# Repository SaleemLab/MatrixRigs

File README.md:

# MatrixRigs
Docs related to setting up and running the matrix rigs

Contents:
- Hardware: wheel, lickport, screens + holders + nvidia mosiac, reward delivery. Parts list.
- Code: bonsai code e.g. screen set up, arduino code + serial read
- Maintenance: flushing reward etc.

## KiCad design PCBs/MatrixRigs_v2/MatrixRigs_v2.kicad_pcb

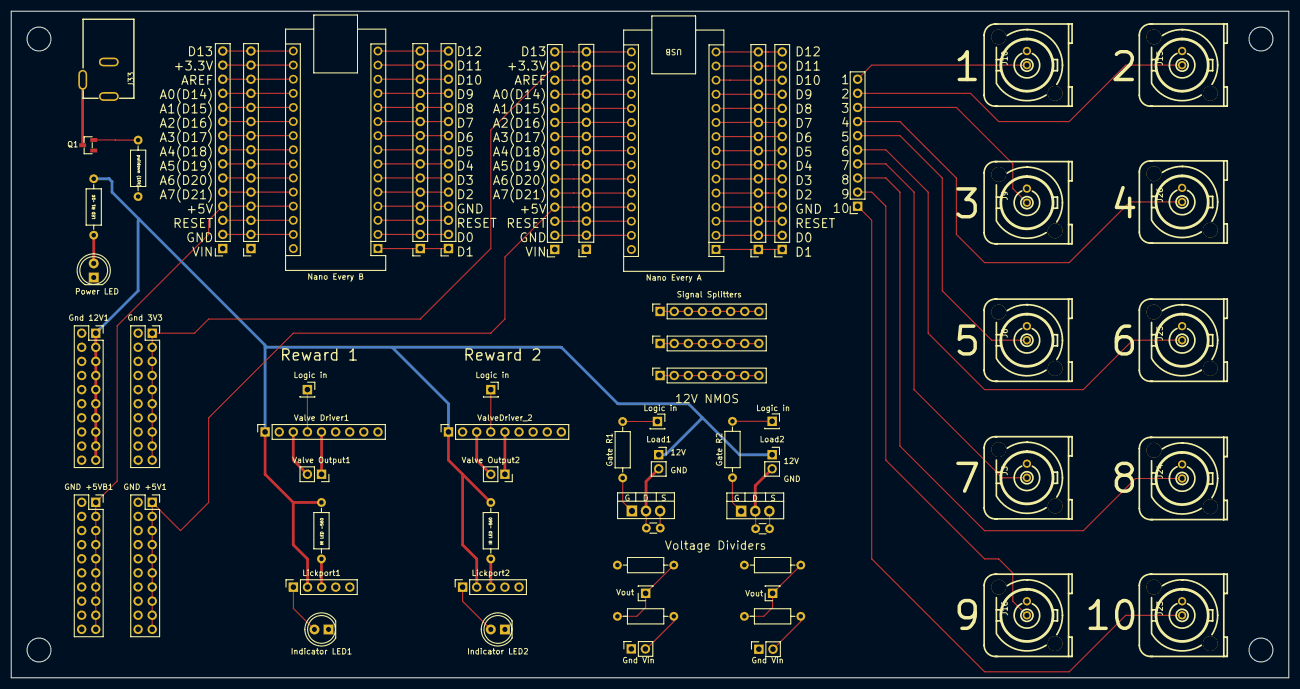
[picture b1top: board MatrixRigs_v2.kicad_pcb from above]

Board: 2 copper layers, 230.0 x 120.0 mm, 67 parts (0 on the bottom side), 92 nets.

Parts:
C1, C2: C; C_Disc_D3.0mm_W1.6mm_P2.50mm
D3: LED; LED_D5.0mm
GND +5V1, GND +5VB1: Conn_02x10_Top_Bottom; PinSocket_2x10_P2.54mm_Vertical
Gate R1, Gate R2: 10-100kohm; R_Axial_DIN0207_L6.3mm_D2.5mm_P10.16mm_Horizontal
Gnd 3V3, Gnd 12V1: Conn_02x10_Top_Bottom; PinSocket_2x10_P2.54mm_Vertical
H1, H2, H3, H4: MountingHole; MountingHole_4.3mm_M4
IR LED -1, IR LED -560: 560ohm; R_Axial_DIN0207_L6.3mm_D2.5mm_P10.16mm_Horizontal
Indicator LED1, Indicator LED2: LED; LED_D5.0mm
J1, J2, J27, J28, J29, J30, J31, J32: Conn_01x15_Socket; PinSocket_1x15_P2.54mm_Vertical
J3, J6, J9, J10, J15, J16, J23, J24, J25, J26: Conn_Coaxial; CONN-TH_1-1337541-0
J4: Conn_01x10_Socket; PinSocket_1x10_P2.54mm_Vertical
J7, J8: Conn_01x01_Socket; PinSocket_1x01_P2.54mm_Vertical
J12, J13: Conn_01x02_Socket; PinSocket_1x02_P2.54mm_Vertical
J33: Barrel_Jack_Switch_Pin3Ring; DC-IN-TH_XDJK-0051-025
LED R1 ~1K: 1kohm; R_Axial_DIN0207_L6.3mm_D2.5mm_P10.16mm_Horizontal
Lickport1, Lickport2: Conn_01x05_Socket; PinSocket_1x05_P2.54mm_Vertical
Load1, Load2: Conn_01x02_Socket; PinSocket_1x02_P2.54mm_Vertical
NMOS-T220: NMOS; TO-220-3_Vertical
Nano Every A: Arduino_Nano_v3.A; Arduino_Nano
Nano Every B: Arduino_Nano_v3.B; Arduino_Nano
Q1: PMOS; SOT-23-3_L2.9-W1.3-P1.90-LS2.4-BR
Q3: NMOS; TO-220-3_Vertical
R8: 10-100kohm; R_Axial_DIN0207_L6.3mm_D2.5mm_P10.16mm_Horizontal
Signal Splitters: Conn_01x08_Pin; PinSocket_1x08_P2.54mm_Vertical
SignalSplitter2, SignalSplitter3: Conn_01x08_Pin; PinSocket_1x08_P2.54mm_Vertical
Valve Driver1: Conn_01x09_Socket; PinSocket_1x09_P2.54mm_Vertical
Valve Output1, Valve Output2: Conn_01x02_Socket; PinSocket_1x02_P2.54mm_Vertical
Valve logic in1, Valve logic in2: Conn_01x01_Socket; PinSocket_1x01_P2.54mm_Vertical
ValveDriver_2: Conn_01x09_Socket; PinSocket_1x09_P2.54mm_Vertical
VoltageDivider_R1_1, VoltageDivider_R1_2: R; R_Axial_DIN0207_L6.3mm_D2.5mm_P10.16mm_Horizontal
VoltageDivider_R2_1: VoltageDivider_R2_1; R_Axial_DIN0207_L6.3mm_D2.5mm_P10.16mm_Horizontal
VoltageDivider_R2_2: VoltageDivider_R2_2; R_Axial_DIN0207_L6.3mm_D2.5mm_P10.16mm_Horizontal
Vout: Conn_01x01_Socket; PinSocket_1x01_P2.54mm_Vertical
Vout#2: Conn_01x01_Socket; PinSocket_1x01_P2.54mm_Vertical

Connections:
+3V3: Gnd 3V3.1, Gnd 3V3.3, Gnd 3V3.5, Gnd 3V3.7, Gnd 3V3.9, Gnd 3V3.11, Gnd 3V3.13, Gnd 3V3.15, Gnd 3V3.17, Gnd 3V3.19, J2.14, J32.14, Nano Every A.17 (3V3)
+3V3_B: J28.14, J30.14, Nano Every B.17 (3V3)
+5V: GND +5V1.1, GND +5V1.3, GND +5V1.5, GND +5V1.7, GND +5V1.9, GND +5V1.11, GND +5V1.13, GND +5V1.15, GND +5V1.17, GND +5V1.19, J2.4, J32.4, Nano Every A.27 (+5V)
+5V_B: GND +5VB1.1, GND +5VB1.3, GND +5VB1.5, GND +5VB1.7, GND +5VB1.9, GND +5VB1.11, GND +5VB1.13, GND +5VB1.15, GND +5VB1.17, GND +5VB1.19, J28.4, J30.4, Nano Every B.27 (+5V)
+12V: Gnd 12V1.1, Gnd 12V1.3, Gnd 12V1.5, Gnd 12V1.7, Gnd 12V1.9, Gnd 12V1.11, Gnd 12V1.13, Gnd 12V1.15, Gnd 12V1.17, Gnd 12V1.19, IR LED -1.1, IR LED -560.1, LED R1 ~1K.1, Lickport1.2, Lickport2.2, Load1.1, Load2.1, Q1.1 (D), Valve Driver1.1, ValveDriver_2.1
A0: J2.12, J32.12, Nano Every A.19 (A0)
A0_B: J28.12, J30.12, Nano Every B.19 (A0)
A1: J2.11, J32.11, Nano Every A.20 (A1)
A1_B: J28.11, J30.11, Nano Every B.20 (A1)
A2: J2.10, J32.10, Nano Every A.21 (A2)
A2_B: J28.10, J30.10, Nano Every B.21 (A2)
A3: J2.9, J32.9, Nano Every A.22 (A3)
A3_B: J28.9, J30.9, Nano Every B.22 (A3)
A4: J2.8, J32.8, Nano Every A.23 (A4)
A4_B: J28.8, J30.8, Nano Every B.23 (A4)
A5: J2.7, J32.7, Nano Every A.24 (A5)
A5_B: J28.7, J30.7, Nano Every B.24 (A5)
A6: J2.6, J32.6, Nano Every A.25 (A6)
A6_B: J28.6, J30.6, Nano Every B.25 (A6)
A7: J2.5, J32.5, Nano Every A.26 (A7)
A7_B: J28.5, J30.5, Nano Every B.26 (A7)
AREF: J2.13, J32.13, Nano Every A.18 (AREF)
AREF_B: J28.13, J30.13, Nano Every B.18 (AREF)
D2: J1.5, J31.5, Nano Every A.5 (D2)
D2_B: J27.5, J29.5, Nano Every B.5 (D2)
D3: J1.6, J31.6, Nano Every A.6 (D3)
D3_B: J27.6, J29.6, Nano Every B.6 (D3)
D4: J1.7, J31.7, Nano Every A.7 (D4)
D4_B: J27.7, J29.7, Nano Every B.7 (D4)
D5: J1.8, J31.8, Nano Every A.8 (D5)
D5_B: J27.8, J29.8, Nano Every B.8 (D5)
D6: J1.9, J31.9, Nano Every A.9 (D6)
D6_B: J27.9, J29.9, Nano Every B.9 (D6)
D7: J1.10, J31.10, Nano Every A.10 (D7)
D7_B: J27.10, J29.10, Nano Every B.10 (D7)
D8: J1.11, J31.11, Nano Every A.11 (D8)
D8_B: J27.11, J29.11, Nano Every B.11 (D8)
D9: J1.12, J31.12, Nano Every A.12 (D9)
D9_B: J27.12, J29.12, Nano Every B.12 (D9)
D10: J1.13, J31.13, Nano Every A.13 (D10)
D10_B: J27.13, J29.13, Nano Every B.13 (D10)
D11: J1.14, J31.14, Nano Every A.14 (D11)
D11_B: J27.14, J29.14, Nano Every B.14 (D11)
D12: J1.15, J31.15, Nano Every A.15 (D12)
D12_B: J27.15, J29.15, Nano Every B.15 (D12)
D13: J2.15, J32.15, Nano Every A.16 (D13)
D13_B: J28.15, J30.15, Nano Every B.16 (D13)
GND: C1.2, C2.2, D3.1 (K), GND +5V1.2, GND +5V1.4, GND +5V1.6, GND +5V1.8, GND +5V1.10, GND +5V1.12, GND +5V1.14, GND +5V1.16, GND +5V1.18, GND +5V1.20, GND +5VB1.2, GND +5VB1.4, GND +5VB1.6, GND +5VB1.8, GND +5VB1.10, GND +5VB1.12, GND +5VB1.14, GND +5VB1.16, GND +5VB1.18, GND +5VB1.20, Gnd 3V3.2, Gnd 3V3.4, Gnd 3V3.6, Gnd 3V3.8, Gnd 3V3.10, Gnd 3V3.12, Gnd 3V3.14, Gnd 3V3.16, Gnd 3V3.18, Gnd 3V3.20, Gnd 12V1.2, Gnd 12V1.4, Gnd 12V1.6, Gnd 12V1.8, Gnd 12V1.10, Gnd 12V1.12, Gnd 12V1.14, Gnd 12V1.16, Gnd 12V1.18, Gnd 12V1.20, Indicator LED1.1 (K), Indicator LED2.1 (K), J1.4, J2.2, J3.2 (Ext), J6.2 (Ext), J9.2 (Ext), J10.2 (Ext), J12.1, J13.1, J15.2 (Ext), J16.2 (Ext), J23.2 (Ext), J24.2 (Ext), J25.2 (Ext), J26.2 (Ext), J27.4, J28.2, J29.4, J30.2, J31.4, J32.2, J33.1, Lickport1.4, Lickport1.5, Lickport2.4, Lickport2.5, NMOS-T220.3 (S), Nano Every A.4 (GND), Nano Every A.29 (GND), Nano Every B.4 (GND), Nano Every B.29 (GND), Q3.3 (S), R8.2, Valve Driver1.2, Valve Driver1.8, ValveDriver_2.2, ValveDriver_2.8, VoltageDivider_R2_1.2, VoltageDivider_R2_2.2
unnamed: D3.2 (A), LED R1 ~1K.2
unnamed: Indicator LED1.2 (A), Lickport1.1
unnamed: Indicator LED2.2 (A), Lickport2.1
unnamed: J3.1 (In), J4.4
unnamed: J4.6, J6.1 (In)
unnamed: J4.8, J9.1 (In)
unnamed: Gate R1.2, J7.1
unnamed: Gate R2.2, J8.1
unnamed: J4.10, J10.1 (In)
unnamed: C2.1, Load2.2, Q3.1 (D)
unnamed: J12.2, VoltageDivider_R1_1.1
unnamed: J13.2, VoltageDivider_R1_2.1
unnamed: J4.9, J15.1 (In)
unnamed: J4.2, J16.1 (In)
unnamed: J4.1, J23.1 (In)
unnamed: J4.3, J24.1 (In)
unnamed: J4.5, J25.1 (In)
unnamed: J4.7, J26.1 (In)
unnamed: IR LED -1.2, Lickport1.3
unnamed: IR LED -560.2, Lickport2.3
unnamed: C1.1, Load1.2, NMOS-T220.1 (D)
unnamed: Gate R1.1, NMOS-T220.2 (G)
unnamed: VoltageDivider_R1_1.2, VoltageDivider_R2_1.1, Vout#2.1
unnamed: VoltageDivider_R1_2.2, VoltageDivider_R2_2.1, Vout.1
unnamed: Q1.2 (G), R8.1
unnamed: J33.3, Q1.3 (S)
unnamed: Gate R2.1, Q3.2 (G)
unnamed: Signal Splitters.1, Signal Splitters.2, Signal Splitters.3, Signal Splitters.4, Signal Splitters.5, Signal Splitters.6, Signal Splitters.7, Signal Splitters.8
unnamed: SignalSplitter2.1, SignalSplitter2.2, SignalSplitter2.3, SignalSplitter2.4, SignalSplitter2.5, SignalSplitter2.6, SignalSplitter2.7, SignalSplitter2.8
unnamed: SignalSplitter3.1, SignalSplitter3.2, SignalSplitter3.3, SignalSplitter3.4, SignalSplitter3.5, SignalSplitter3.6, SignalSplitter3.7, SignalSplitter3.8
unnamed: Valve Driver1.3, Valve Output1.2
unnamed: Valve Driver1.4, Valve logic in1.1
unnamed: Valve Driver1.5, Valve Output1.1
unnamed: Valve Output2.1, ValveDriver_2.5
unnamed: Valve Output2.2, ValveDriver_2.3
unnamed: Valve logic in2.1, ValveDriver_2.4
RST: J1.3, J2.3, J31.3, J32.3, Nano Every A.3 (~RESET), Nano Every A.28 (~RESET)
RST_B: J27.3, J28.3, J29.3, J30.3, Nano Every B.3 (~RESET), Nano Every B.28 (~RESET)
RX0: J1.2, J31.2, Nano Every A.2 (D0/RX)
RX0_B: J27.2, J29.2, Nano Every B.2 (D0/RX)
TX1: J1.1, J31.1, Nano Every A.1 (D1/TX)
TX1_B: J27.1, J29.1, Nano Every B.1 (D1/TX)
VIN: J2.1, J32.1
VIN_B: J28.1, J30.1

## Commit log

2023-02-14 Update README.md
    started future contents list
2023-02-14 Added lickport calibration workflow
    Need to update to automate serial com
2023-02-14 3d printing: lickport and screen holder files
2023-02-17 Added some 3d printing files
2023-03-02 added leonardo arduino code
2023-03-07 camera holder stl files
2023-03-13 ArduinoNanoEvery code
2023-05-30 camera driver
2023-05-30 Create drivers directory
2023-06-08 WIP update on lickport calibration code
2023-06-08 WIP update to lickport cal
2023-06-09 Lickport Calibration workflow
    Workflow to perform automated open time vs reward volume collection completed, need to test on rig itself.
    Step remaining: Matlab/python script to generate LUT + integrate bonsai code for mapping reward volume to valve open time
2023-06-20 Created matlab script for lickport calibration
2023-08-10 automated lickport calibration
2023-09-12 updated arduino code to set sample rate on-board
2023-12-20 New camera holder stl file
2023-12-20 removed depreciated 3d printed files
2024-01-17 Update ArduinoNanoEvery_chronicEphys2024.ino
    added photidode signal to arduino
2024-03-10 arduino code and lickport cal (not tested)
2024-03-11 Testing with externalised breadboard
2024-03-12 some 3rd party 3d printing + lens adjustmen pdf
2024-03-15 Simple flush reward workflow
2024-03-15 Clean up repo structure
2024-03-18 Fixed TestPeripherals workflow (condition)
2024-03-20 tested lickport calibration working
2024-03-27 some 3d printed files
2024-03-28 lickport calibration and mouse weight matlab files
2024-04-09 tets
2024-04-12 Example csv logging w nice formatting
2024-04-12 Arduino code for 2p room
    Modified ArduinoNanoEvery_chronicEphys2024 code to include 2p frame trigger and line scanner.
2024-04-15 dev arduino code
2024-04-16 update to dev arduino code
2024-04-16 basic arudino parse
2024-04-18 Added local copy of Bonsai 2.7.3
2024-04-19 Changed photodiode pin to A0
2024-04-22 photodiode holder 3d printed part
2024-04-22 clean up photodiode holder files
2024-04-29 Update ArduinoNanoEvery_2P_April2024.ino
    Converted to times and synched with Edd's code
2024-04-29 upload ffmeg
2024-05-01 organised arduino code
2024-05-09 added dev pcb design
2024-05-10 sparse noise stimulus (dev)
2024-05-10 added checkerboard (dev)
2024-05-13 AS version of sparse noise on 3 screens
2024-05-15 added logging to checkerboard
2024-05-15 vis stim updates
2024-06-11 Sync pluse pin change
2024-06-11 push visual stimuli
2024-06-14 Updated DotMotion_FastSpeedChanges
2024-06-14 gratingsAndPlaids RSVP stimulus (WIP)
2024-06-27 edds stim - flicker, contrast switching, RSVP
2024-06-27 Revert "edds stim - flicker, contrast switching, RSVP"
    This reverts commit 40a11db5337a7b6585ac19f30dad4f0a7c345fc9.
2024-07-09 Update SyncPulse_2P_April24.ino
    changed encoder pinOUT
2024-07-09 Create triggered_screen_blanker_teensy.ino
    Trigger display off during 2p bidirectional scanning
2024-07-09 improved logging headers for dotmotion stimulus (only updated speed tuning)
2024-07-09 Edd stimulus update
    Long overdue push of stimulus updates from the unit (no internet connection in there)
2024-07-09 added left/right options to speed tgunbing
2024-07-10 Create ArduinoNanoEvery_2P_July2024.ino
    Reads pd pin only when display flicker is on.
2024-07-12 added general dot motion (2d) stimulus
2024-07-30 fixed disabled trial params + updated to state-dependent stim pres
2024-08-09 work on state-dependent stimulus presentation
2024-08-09 state-dependent stim presentation wip
    stat
2024-08-12 PD fix
    Takes the average PD value across the 100 microsecond refreshes
2024-08-12 state-dependent stim presentation - basic orientation example
2024-08-12 update state-dependent stim pres (ori example)
2024-08-13 DotMotion-stateDependentStim - basic working
    WIP.
    Also some clean up of DotMotion-General workflow.
2024-08-13 added blank trials to State-dependent dot motion stim
2024-08-13 pause + quit function in state-dependent dot motion stim
    to do: add logging of speed/contrast with standard params
2024-08-13 logging and rename state stim
2024-08-14 Added behavioural state classification of trials to AdaptiveStimControl
    to do: add 3rd state for trials that satisfy neither stationary or locomotion criteria
2024-10-11 backlight modulation work
2024-10-11 Revert "up"
    This reverts commit ffe596f0238574f0f3c72b04ca32583562bd0579, reversing
    changes made to 65146b36a44e8ffa1089c2f424d7094981012d8a.
2024-10-11 Fixed state-dependent dot motion bug
2024-10-11 2pin arduino flicker
2024-11-11 added 'set PWM brightness' to Arduino LED code
2024-11-12 Update to arduino PWM control - faster PWM and proper(ish) sinusoids
2024-11-12 Sine dimming with slower contrast envelope
2024-11-18 July updates
    Sampling frequency changed to 120 and photodiodereadcounter added to find mean PD value to serial write.
2024-11-21 added mkdir to GenerateWeightAgeTable in case MouseData does not exist
2024-12-03 added "-1" stimulus ended flag to leonardo stimulus control
2024-12-03 LED white noise and frozen white noise stim
2024-12-18 toggle pin 4 for frozen white noise duty cycle change
2025-01-24 state dependent stim edd
2025-01-24 fixed NAN issue in state-dependent stim presentaiton
2025-01-24 fixed 0 contrast flash issue (hopefully)
2025-01-31 state-dependent save (no major changes)
2025-01-31 state dependent ganzfeld stim, wip
2025-01-31 serial string write working for ganzfeld state dependent
2025-02-24 Teensy code V2
    Trigger on rise (fall disabled)
2025-03-11 Create SyncPulse_2P_March25.ino
    Changed serial begin and read
2025-03-25 wip ganzfeld state-dependent
2025-03-25 wip ganzfeld state dependent
2025-03-25 ganzfeld state-dependent random sampling working
2025-03-25 state-dependent ganzfeld working for dist 1
    random for dist 2 atm?
2025-03-25 state-dependent ganzfeld working
2025-03-25 sineEnvelope state-dependent
2025-03-26 edd wip on sylvias rig (temp files)
2025-03-26 state-dependent ganzfeld stim working on sylvias rig
2025-04-03 Piezo Arduino added
2025-04-10 Create EyeTrackingArduino_SyncReceiver_April2025.ino
    Eye tracking async pulse receiver
2025-04-11 Added TwoPFrameTime to EyeTracking Arduino
2025-04-11 updated delay rising and falling values.
2025-04-13 updated delay rise/fall for max zoom
2025-04-14 Create MatrixRigs_Arduino_2025.ino
    Updated base matrix rigs arudino code (not yet uploaded)
    Main changes:
    - rotary encoder processing now uses quadrature encoding (i.e. 4096 ticks/revolution)
    - cleaned up serial input, improved parsing of reward times. Now use "r,400" for 400ms right valve open time
2025-04-15 integrated sync pulse into new arduino code
    no need to have separate arudino for this with non-blocking code
2025-04-20 removed TwoPFrameTime from EyeCamSync
2025-04-29 implemented saving dir location on example workflow
2025-05-01 pcb up
2025-05-08 removed duplicate sync pins - can split externally instead
2025-05-08 Create MatrixRigs_Arduino_wCameraGPIO_2025.ino
    new arduino code for led stimulator rig, incorporate frame time logging on nano
2025-05-09 base workflow for led stim experiments
    nb. will port to correct repo
2025-05-16 basic sinewave stim workflow for led stimulatior
2025-05-30 removed LED stimuli from repo
2025-06-04 remove backlight stimuli
    f
2025-06-06 fixed formatting bug in new arduino code
2025-06-10 move led stimuli to archive
2025-06-10 basic logging
2025-06-10 add gitignore
2025-06-10 updated sparse noise logging
2025-06-10 updated checkerboard logging
2025-06-10 updating logging
2025-06-11 state-dependent motion coherence
2025-06-12 DotCorridor stimuli for passive phys
2025-07-01 dot corridor stimuli
2025-07-10 Add DotCorridor_Replay workflow and update ClosedLoop
    Added new DotCorridor_Replay.bonsai and layout files for replay functionality. Updated DotCorridor_ClosedLoop.bonsai to set VelocityX to 0, changed file naming and output directory logic, added key i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
2025-07-10 WheelGain parameter in closed-loop dotcorridor
2025-07-10 Add DotCorridor_ClosedLoop_Perturbations and update quad state
    Quad state behaviour adjusted so always goes to 1 when dot corridor stimulus initiates (i.e. first render frame of stim has quad state ==1)
2025-07-25 work f;pow
2025-07-25 fix dot corridor workflows
2025-08-07 added repeat sequence count var for FastSpeedChanges stim
2025-08-21 checked gamma correction applied to stimuli
2025-10-14 manual lickport cal
2025-10-20 fixed flush workflow
2025-12-04 3screen example
2025-12-06 changed async pin
2025-12-06 async pin changed
2025-12-11 added simple drifting gratings direction tuning workflow
    bit hacky adapting the gratings/plaids workflow, but just sets gratings2 to 0 contrast.
2025-12-12 Aida stim M125
2026-01-23 changed frame trig pin
    - pin 9 was dropping frame time for some odd reason.
    - fine using D5
